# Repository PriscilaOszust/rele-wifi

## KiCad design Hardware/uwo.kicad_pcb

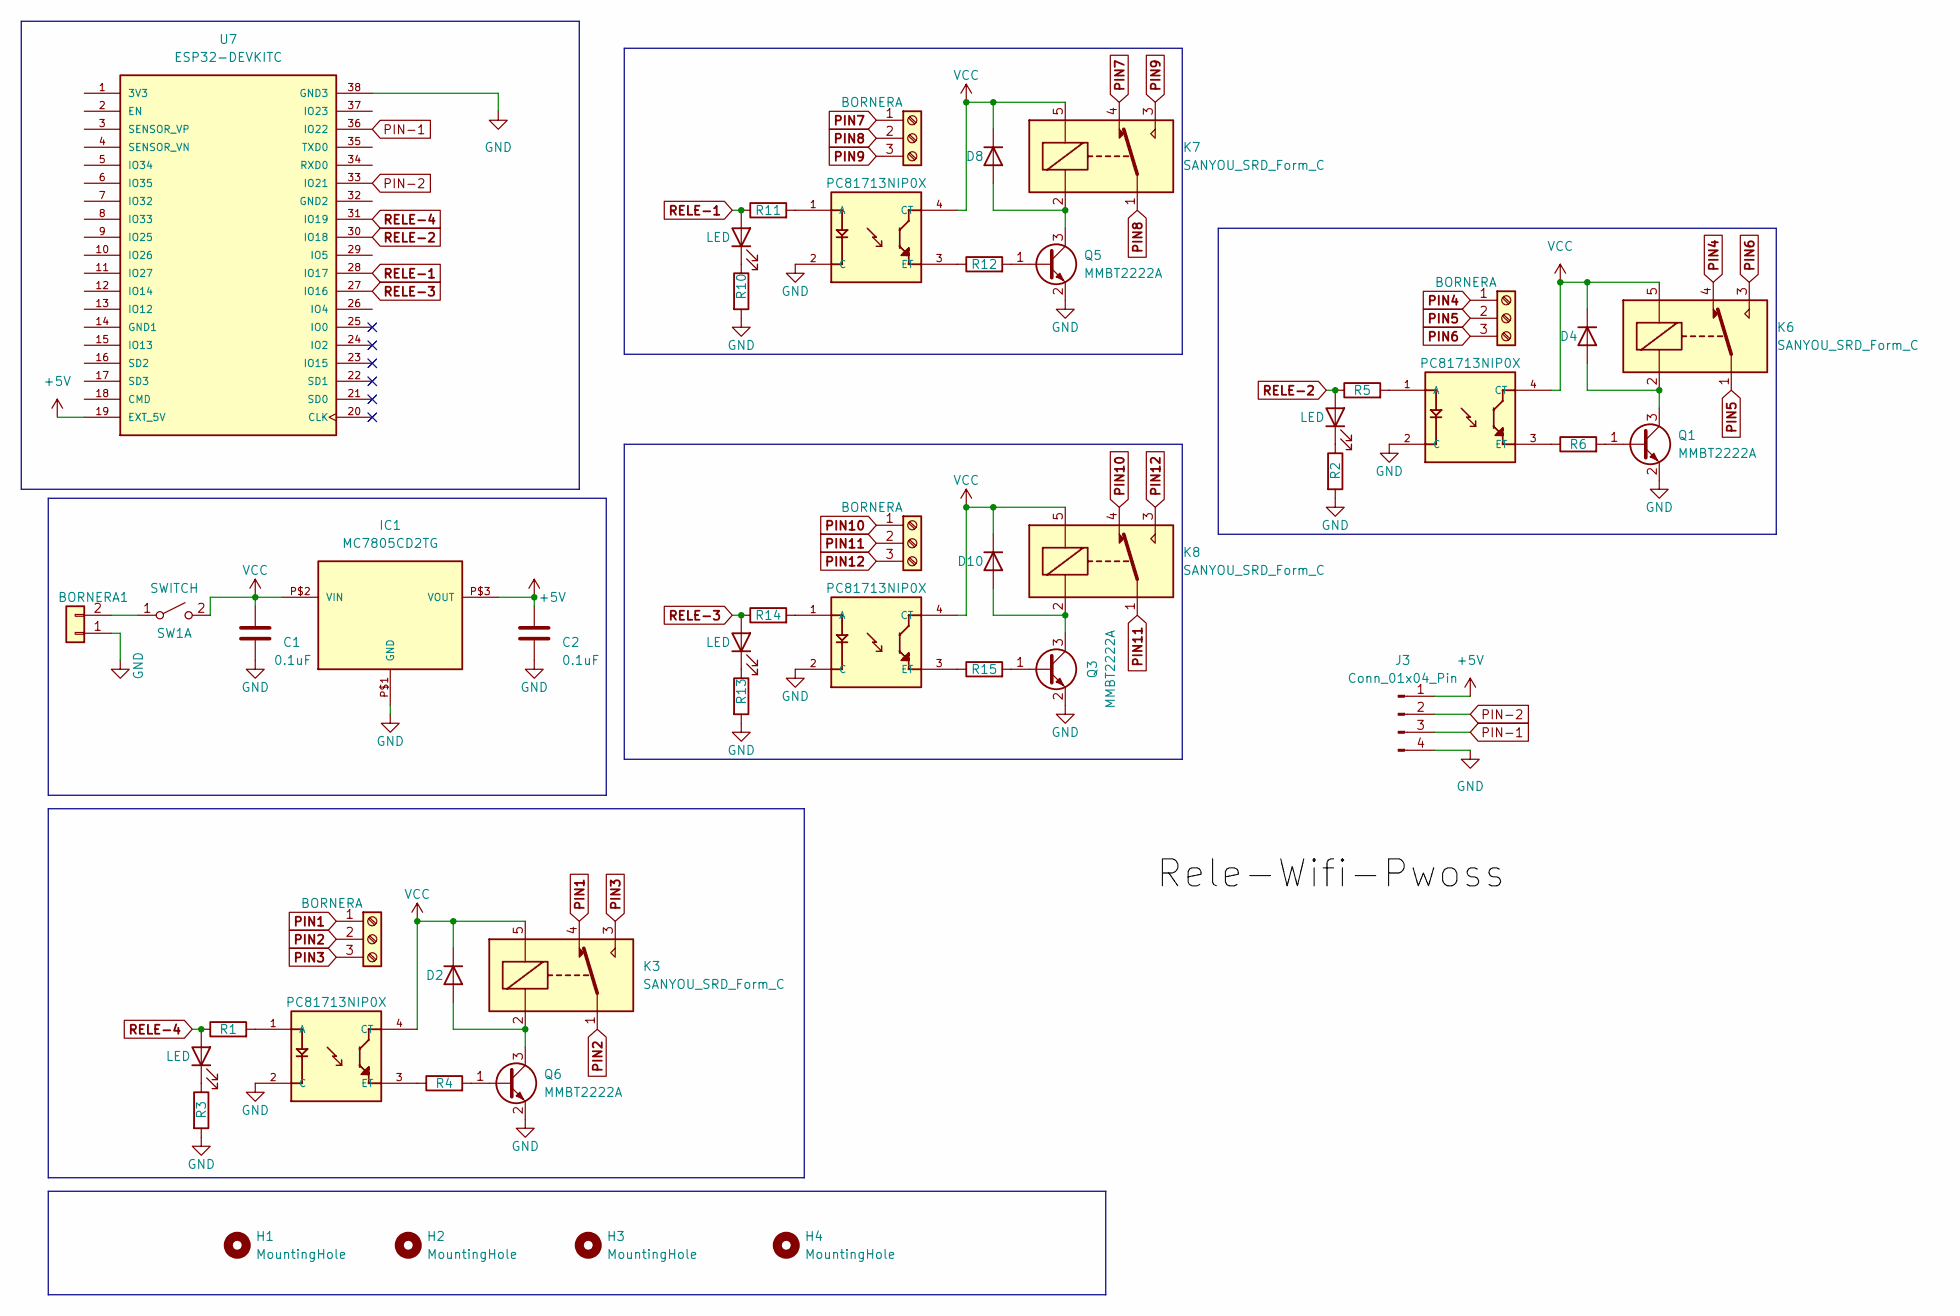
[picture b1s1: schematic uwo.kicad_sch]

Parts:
BORNERA1: TerminalBlock_bornier-2_P5.08mm
C1, C2: 0.1uF; C_0805_2012Metric
D1, D3, D7, D9: LED; LED_0805_2012Metric_Pad1.15x1.40mm_HandSolder
D2, D4, D8, D10: D; D_SMA
H1, H2, H3, H4: MountingHole; MountingHole_3.2mm_M3
IC1: MC7805CD2TG
J1, J2, J4, J5: BORNERA; TerminalBlock_bornier-3_P5.08mm
J3: Conn_01x04_Pin; PinSocket_1x04_P2.54mm_Vertical
K3, K6, K7, K8: SANYOU_SRD_Form_C; Relay_SPDT_SANYOU_SRD_Series_Form_C
Q1, Q3, Q5, Q6: MMBT2222A; SOT-23
R1, R2, R3, R4, R5, R6, R10, R11, R12, R13, R14, R15: R; R_0805_2012Metric
SW1: SWITCH; PinHeader_1x02_P2.54mm_Vertical
U1, U2, U4, U5: PC81713NIP0X; SOT254P1025X400-4N
U7: ESP32-DEVKITC; MODULE_ESP32-DEVKITC; PARTREV N/A

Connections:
+5V: C2.1, IC1.P$3 (VOUT), J3.1, U7.19 (EXT_5V)
GND: BORNERA1.1, C1.2, C2.2, IC1.P$1 (GND), J3.4, Q1.2 (E), Q3.2 (E), Q5.2 (E), Q6.2 (E), R2.2, R3.2, R10.2, R13.2, U1.2 (C), U2.2 (C), U4.2 (C), U5.2 (C), U7.38 (GND3)
unnamed: BORNERA1.2, SW1.1 (A)
unnamed: D1.1 (K), R2.1
unnamed: D2.2 (A), K3.2, Q6.3 (C)
unnamed: D3.1 (K), R3.1
unnamed: D4.2 (A), K6.2, Q1.3 (C)
unnamed: D7.1 (K), R10.1
unnamed: D8.2 (A), K7.2, Q5.3 (C)
unnamed: D9.1 (K), R13.1
unnamed: D10.2 (A), K8.2, Q3.3 (C)
unnamed: Q1.1 (B), R6.2
unnamed: Q3.1 (B), R15.2
unnamed: Q5.1 (B), R12.2
unnamed: Q6.1 (B), R4.2
unnamed: R1.2, U1.1 (A)
unnamed: R4.1, U1.3 (ET)
unnamed: R5.2, U2.1 (A)
unnamed: R6.1, U2.3 (ET)
unnamed: R11.2, U4.1 (A)
unnamed: R12.1, U4.3 (ET)
unnamed: R14.2, U5.1 (A)
unnamed: R15.1, U5.3 (ET)
PIN1: J1.1, K3.4
PIN2: J1.2, K3.1
PIN3: J1.3, K3.3
PIN4: J2.1, K6.4
PIN5: J2.2, K6.1
PIN6: J2.3, K6.3
PIN7: J4.1, K7.4
PIN8: J4.2, K7.1
PIN9: J4.3, K7.3
PIN10: J5.1, K8.4
PIN11: J5.2, K8.1
PIN12: J5.3, K8.3
PIN-1: J3.3, U7.36 (IO22)
PIN-2: J3.2, U7.33 (IO21)
RELE-1: D7.2 (A), R11.1, U7.28 (IO17)
RELE-2: D1.2 (A), R5.1, U7.30 (IO18)
RELE-3: D9.2 (A), R14.1, U7.27 (IO16)
RELE-4: D3.2 (A), R1.1, U7.31 (IO19)
VCC: C1.1, D2.1 (K), D4.1 (K), D8.1 (K), D10.1 (K), IC1.P$2 (VIN), K3.5, K6.5, K7.5, K8.5, SW1.2 (B), U1.4 (CT), U2.4 (CT), U4.4 (CT), U5.4 (CT)

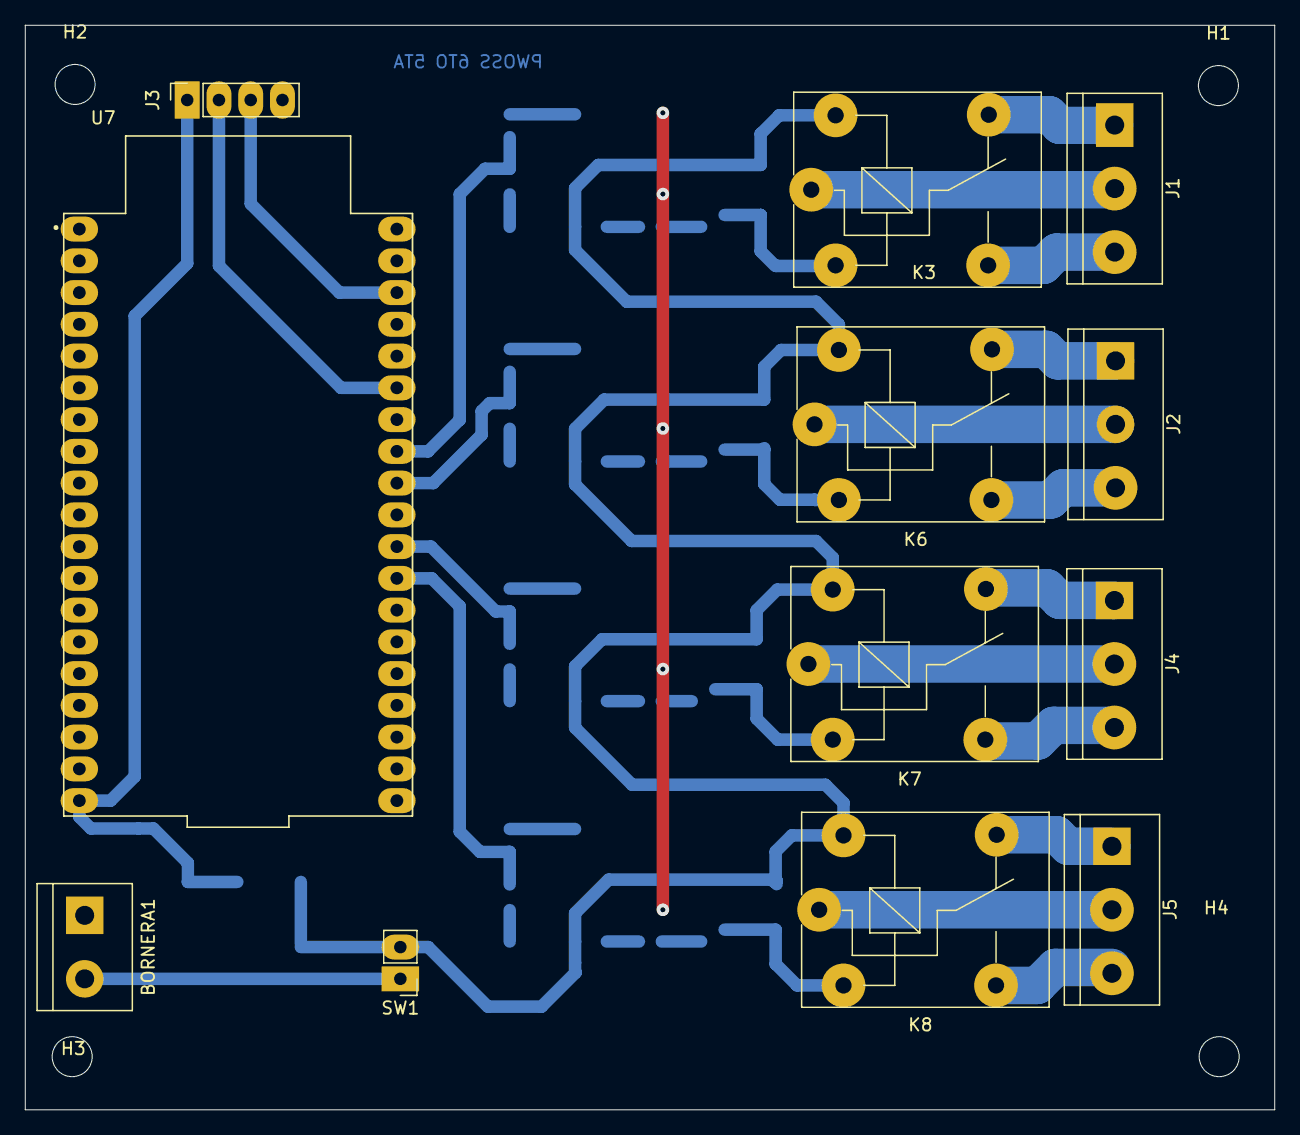
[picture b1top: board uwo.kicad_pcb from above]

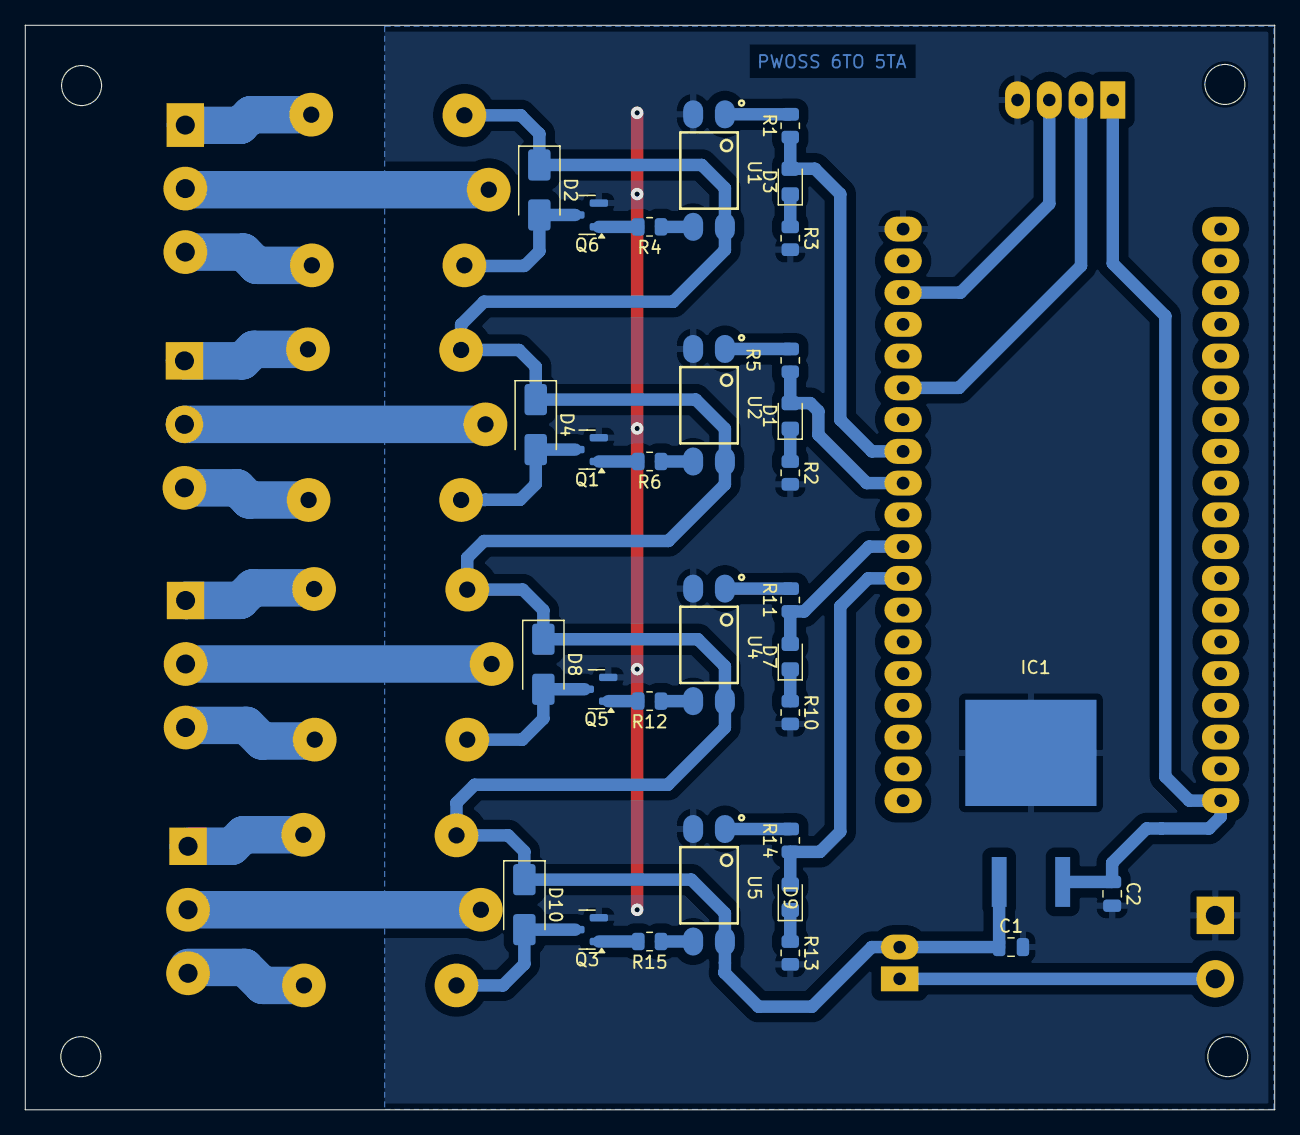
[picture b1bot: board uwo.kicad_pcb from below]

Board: 2 copper layers, 99.9 x 86.8 mm, 47 parts (31 on the bottom side), 42 nets.

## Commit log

2025-03-28 modificamos titulo en index.html
2025-03-28 Añadi carpeta
2025-03-28 Agregue carpeta Hardware
2025-03-28 Agregue nueva carpeta
2025-08-12 Add files via upload
    ULTIMO AVANCE DE PCB Y ESQUEMATICO 12/8/25
2025-08-12 Add files via upload
    ULTIMO AVANCE DEL RELE WIFI 12/8/2025 "UWO"
